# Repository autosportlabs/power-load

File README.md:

# power-load
PCB to mount multiple 10W power resistors (ARCOL RWS10)

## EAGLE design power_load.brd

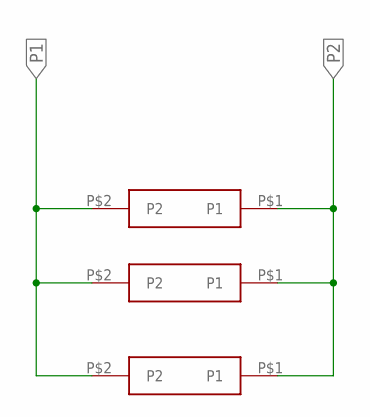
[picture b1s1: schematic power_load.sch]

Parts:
U$1, U$2, U$3: ARCOL_10W; 10W_ARCOL

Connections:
P1: U$1.P$2 (P2), U$2.P$2 (P2), U$3.P$2 (P2)
P2: U$1.P$1 (P1), U$2.P$1 (P1), U$3.P$1 (P1)

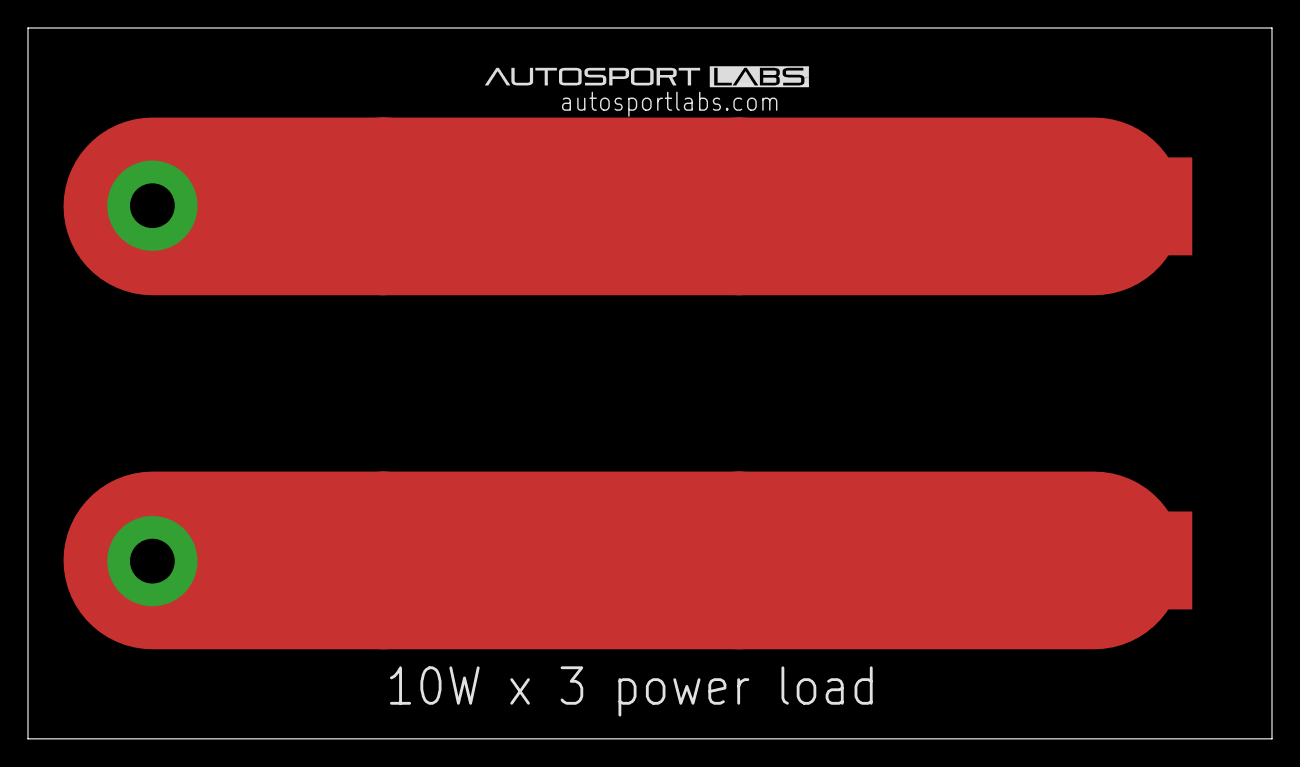
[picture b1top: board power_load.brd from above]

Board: 2 copper layers, 88.9 x 50.8 mm, 3 parts (0 on the bottom side), 2 nets.

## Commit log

2017-01-15 add board / schematics
